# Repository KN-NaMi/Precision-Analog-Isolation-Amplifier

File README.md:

# Precision-Analog-Isolation-Amplifier

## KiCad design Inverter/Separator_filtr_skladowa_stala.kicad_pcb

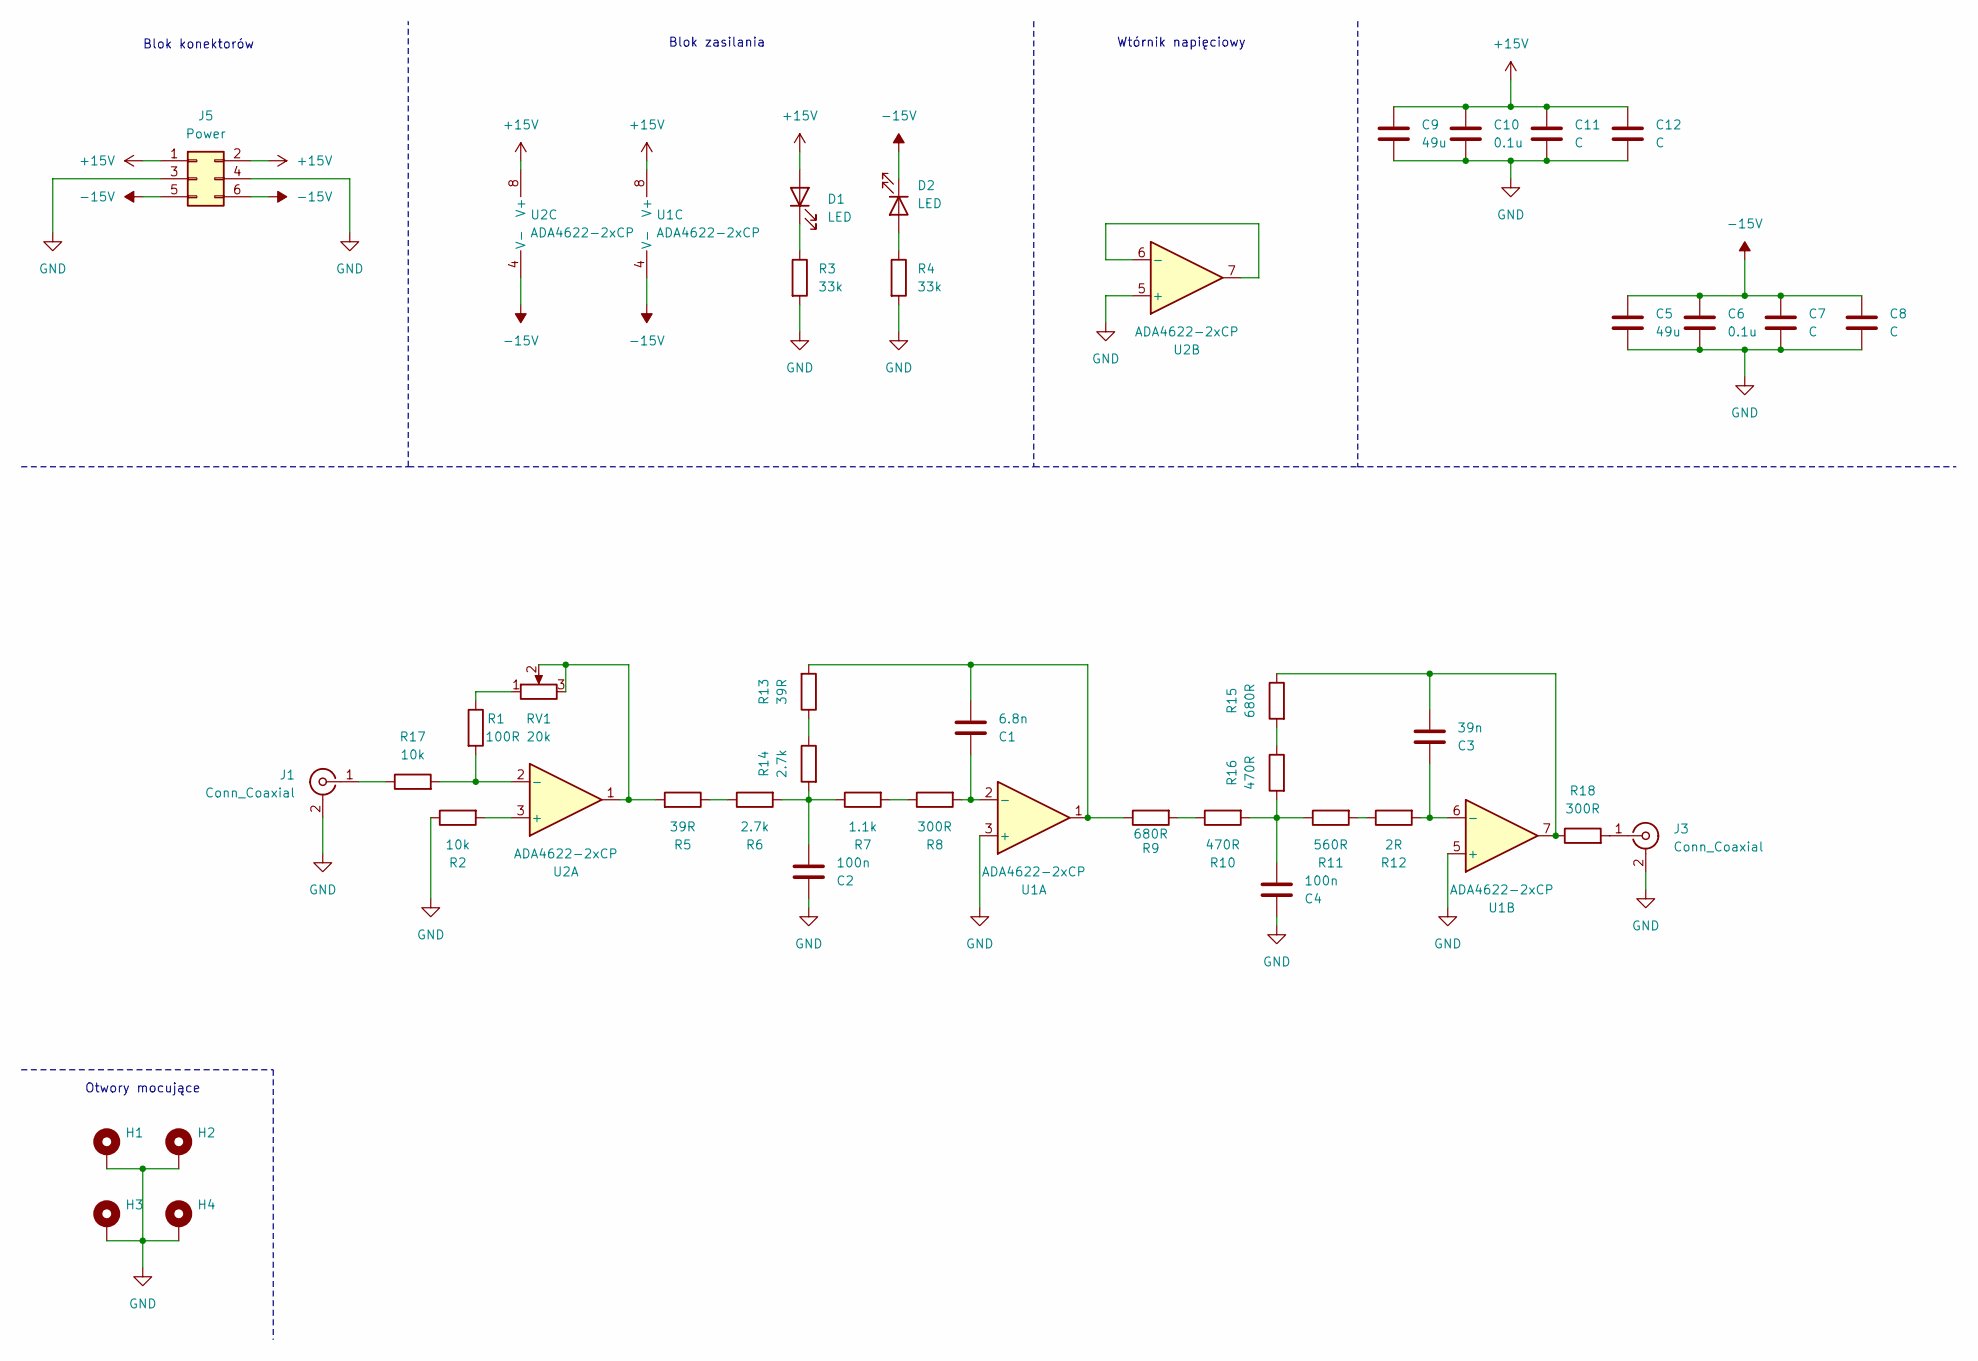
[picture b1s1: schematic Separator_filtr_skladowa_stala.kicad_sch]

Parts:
C1: 6.8n; C_0805_2012Metric_Pad1.18x1.45mm_HandSolder
C2, C4: 100n; C_0805_2012Metric_Pad1.18x1.45mm_HandSolder
C3: 39n; C_0805_2012Metric_Pad1.18x1.45mm_HandSolder
C5, C9: 49u; C_0805_2012Metric_Pad1.18x1.45mm_HandSolder
C6, C10: 0.1u; C_0805_2012Metric_Pad1.18x1.45mm_HandSolder
C7, C8, C11, C12: C; C_0805_2012Metric_Pad1.18x1.45mm_HandSolder
D1, D2: LED; LED_0805_2012Metric_Pad1.15x1.40mm_HandSolder
H1, H2, H3, H4: MountingHole_Pad; MountingHole_3.2mm_M3_DIN965_Pad
J1, J3: Conn_Coaxial; CONN_732511350_MOL
J5: Power; PinHeader_2x03_P2.54mm_Vertical
R1: 100R; R_0805_2012Metric_Pad1.20x1.40mm_HandSolder
R2, R17: 10k; R_0805_2012Metric_Pad1.20x1.40mm_HandSolder
R3, R4: 33k; R_0805_2012Metric_Pad1.20x1.40mm_HandSolder
R5, R13: 39R; R_0805_2012Metric_Pad1.20x1.40mm_HandSolder
R6, R14: 2.7k; R_0805_2012Metric_Pad1.20x1.40mm_HandSolder
R7: 1.1k; R_0805_2012Metric_Pad1.20x1.40mm_HandSolder
R8, R18: 300R; R_0805_2012Metric_Pad1.20x1.40mm_HandSolder
R9, R15: 680R; R_0805_2012Metric_Pad1.20x1.40mm_HandSolder
R10, R16: 470R; R_0805_2012Metric_Pad1.20x1.40mm_HandSolder
R11: 560R; R_0805_2012Metric_Pad1.20x1.40mm_HandSolder
R12: 2R; R_0805_2012Metric_Pad1.20x1.40mm_HandSolder
RV1: 20k; Potentiometer_Bourns_3386W_Horizontal
U1, U2: ADA4622-2xCP; SOIC127P600X175-8N

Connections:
+15V: C9.1, C10.1, C11.1, C12.1, D1.2 (A), J5.1, J5.2, U1.8 (V+), U1.9 (V+), U2.8 (V+), U2.9 (V+)
-15V: C5.1, C6.1, C7.1, C8.1, D2.1 (K), J5.5, J5.6, U1.4 (V-), U2.4 (V-)
GND: C2.1, C4.1, C5.2, C6.2, C7.2, C8.2, C9.2, C10.2, C11.2, C12.2, H1.1, H2.1, H3.1, H4.1, J1.2 (Ext), J1.3, J1.4, J1.5, J3.2 (Ext), J3.3, J3.4, J3.5, J5.3, J5.4, R2.1, R3.2, R4.2, U1.3 (+), U1.5 (+), U2.5 (+)
unnamed: C1.2, R9.1, R13.2, U1.1
unnamed: C2.2, R6.2, R7.1, R14.2
unnamed: C3.2, R15.1, R18.1, U1.7
unnamed: C4.2, R10.2, R11.1, R16.2
unnamed: D1.1 (K), R3.1
unnamed: D2.2 (A), R4.1
unnamed: J1.1 (In), R17.1
unnamed: J3.1 (In), R18.2
unnamed: R1.1, RV1.1
unnamed: R5.1, R6.1
unnamed: R5.2, RV1.2, RV1.3, U2.1
unnamed: R7.2, R8.1
unnamed: R9.2, R10.1
unnamed: R11.2, R12.1
unnamed: R13.1, R14.1
unnamed: R15.2, R16.1
unnamed: C1.1, R8.2, U1.2 (-)
unnamed: C3.1, R12.2, U1.6 (-)
unnamed: R2.2, U2.3 (+)
unnamed: R1.2, R17.2, U2.2 (-)
unnamed: U2.6 (-), U2.7

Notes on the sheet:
Otwory mocujące
Blok zasilania
Wtórnik napięciowy
Blok konektorów

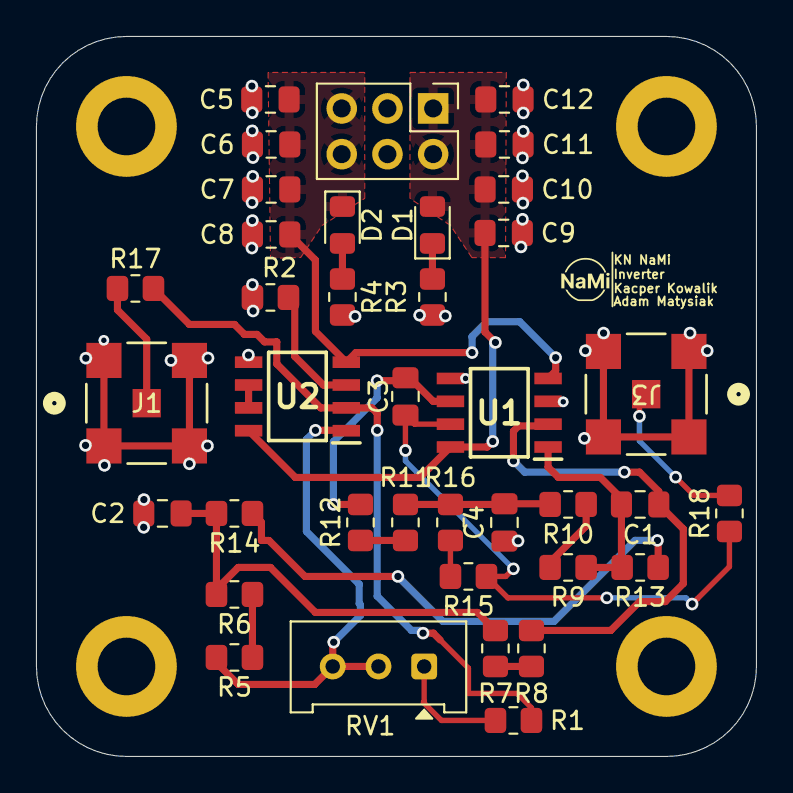
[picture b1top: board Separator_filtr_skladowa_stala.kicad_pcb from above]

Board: 2 copper layers, 40.0 x 40.0 mm, 42 parts (0 on the bottom side), 24 nets.

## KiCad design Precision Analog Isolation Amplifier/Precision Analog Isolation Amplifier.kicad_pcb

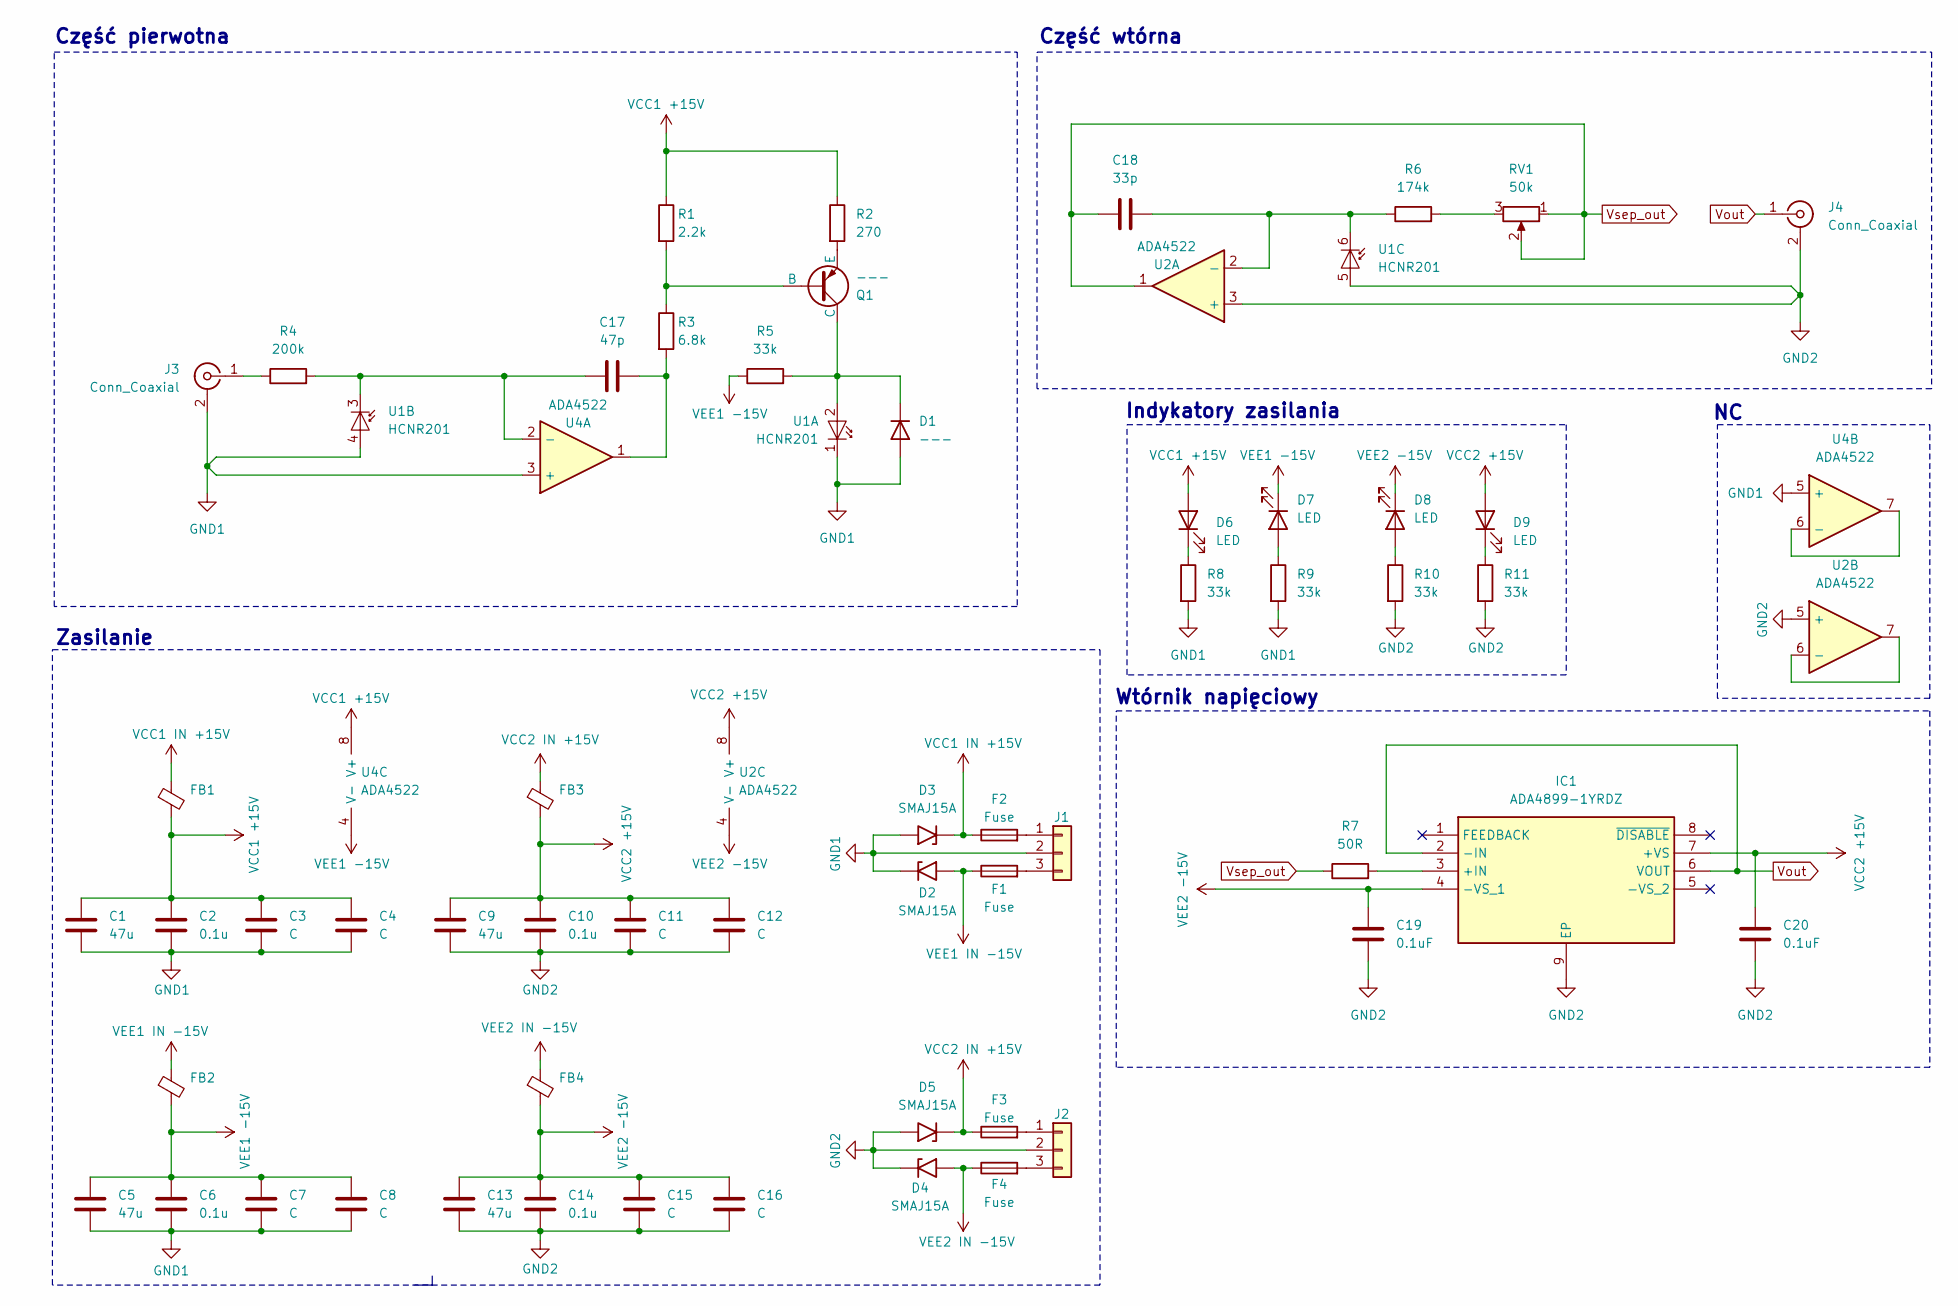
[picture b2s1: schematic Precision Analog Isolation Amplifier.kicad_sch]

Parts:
C1, C5, C9, C13: 47u; C_0805_2012Metric_Pad1.18x1.45mm_HandSolder
C2, C6, C10, C14: 0.1u; C_0805_2012Metric_Pad1.18x1.45mm_HandSolder
C3, C4, C7, C8, C11, C12, C15, C16: C; C_0805_2012Metric_Pad1.18x1.45mm_HandSolder
C17: 47p; C_0805_2012Metric_Pad1.18x1.45mm_HandSolder
C18: 33p; C_0805_2012Metric_Pad1.18x1.45mm_HandSolder
C19, C20: 0.1uF; C_0805_2012Metric_Pad1.18x1.45mm_HandSolder
D1: ---; D_0805_2012Metric_Pad1.15x1.40mm_HandSolder
D2, D3, D4, D5: SMAJ15A; D_SMA
D6, D7, D8, D9: LED; D_0805_2012Metric_Pad1.15x1.40mm_HandSolder
F1, F2, F3, F4: Fuse; R_0805_2012Metric_Pad1.20x1.40mm_HandSolder
FB1, FB2, FB3, FB4: FerriteBead_Small; L_1206_3216Metric
IC1: ADA4899-1YRDZ; SOIC127P600X175-9N; Mouser Part Number 584-ADA4899-1YRDZ
J1, J2: Conn_01x03; PinHeader_1x03_P2.54mm_Vertical
J3, J4: Conn_Coaxial; CONN_732511350_MOL
Q1: ---; SOT-23_Handsoldering
R1: 2.2k; R_0805_2012Metric_Pad1.20x1.40mm_HandSolder
R2: 270; R_0805_2012Metric_Pad1.20x1.40mm_HandSolder
R3: 6.8k; R_0805_2012Metric_Pad1.20x1.40mm_HandSolder
R4: 200k; R_0805_2012Metric_Pad1.20x1.40mm_HandSolder
R5, R8, R9, R10, R11: 33k; R_0805_2012Metric_Pad1.20x1.40mm_HandSolder
R6: 174k; R_0805_2012Metric_Pad1.20x1.40mm_HandSolder
R7: 50R; R_0805_2012Metric_Pad1.20x1.40mm_HandSolder
RV1: 50k; Potentiometer_Bourns_3386W_Horizontal
U1: HCNR201; HCNR201300E
U2, U4: ADA4522; SOIC127P600X175-8N

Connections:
GND1: C1.1, C2.1, C3.1, C4.1, C5.1, C6.1, C7.1, C8.1, D1.2 (A), D2.1 (A1), D3.2 (A2), J1.2, J3.2 (Ext), J3.3, J3.4, J3.5, R8.2, R9.2, U1.1 (K), U1.4 (A), U4.3 (+), U4.5 (+)
GND2: C9.1, C10.1, C11.1, C12.1, C13.1, C14.1, C15.1, C16.1, C19.1, C20.1, D4.1 (A1), D5.2 (A2), IC1.9 (EP), J2.2, J4.2 (Ext), J4.3, J4.4, J4.5, R10.2, R11.2, U1.5 (A), U2.3 (+), U2.5 (+)
unnamed: C17.2, R3.2, U4.1
unnamed: D1.1 (K), Q1.1 (C), R5.2, U1.2 (A)
unnamed: D6.1 (K), R8.1
unnamed: D7.2 (A), R9.1
unnamed: D8.2 (A), R10.1
unnamed: D9.1 (K), R11.1
unnamed: IC1.3 (+IN), R7.2
unnamed: F2.2, J1.1
unnamed: F1.2, J1.3
unnamed: F3.2, J2.1
unnamed: F4.2, J2.3
unnamed: J3.1 (In), R4.1
unnamed: Q1.2 (B), R1.2, R3.1
unnamed: Q1.3 (E), R2.2
unnamed: R6.2, RV1.3
unnamed: C17.1, R4.2, U1.3 (K), U4.2 (-)
unnamed: C18.2, R6.1, U1.6 (K), U2.2 (-)
unnamed: U2.6 (-), U2.7
unnamed: U4.6 (-), U4.7
VCC1 +15V: C1.2, C2.2, C3.2, C4.2, D6.2 (A), FB1.2, R1.1, R2.1, U4.8 (V+)
VCC1 IN +15V: D3.1 (A1), F2.1, FB1.1
VCC2 +15V: C9.2, C10.2, C11.2, C12.2, C20.2, D9.2 (A), FB3.2, IC1.7 (+VS), U2.8 (V+)
VCC2 IN +15V: D5.1 (A1), F3.1, FB3.1
VEE1 -15V: C5.2, C6.2, C7.2, C8.2, D7.1 (K), FB2.2, R5.1, U4.4 (V-)
VEE1 IN -15V: D2.2 (A2), F1.1, FB2.1
VEE2 -15V: C13.2, C14.2, C15.2, C16.2, C19.2, D8.1 (K), FB4.2, IC1.4 (-VS_1), U2.4 (V-)
VEE2 IN -15V: D4.2 (A2), F4.1, FB4.1
Vout: IC1.2 (-IN), IC1.6 (VOUT), J4.1 (In)
Vsep_out: C18.1, R7.1, RV1.1, RV1.2, U2.1

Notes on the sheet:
Zasilanie
Część pierwotna
Wtórnik napięciowy
Indykatory zasilania
Część wtórna

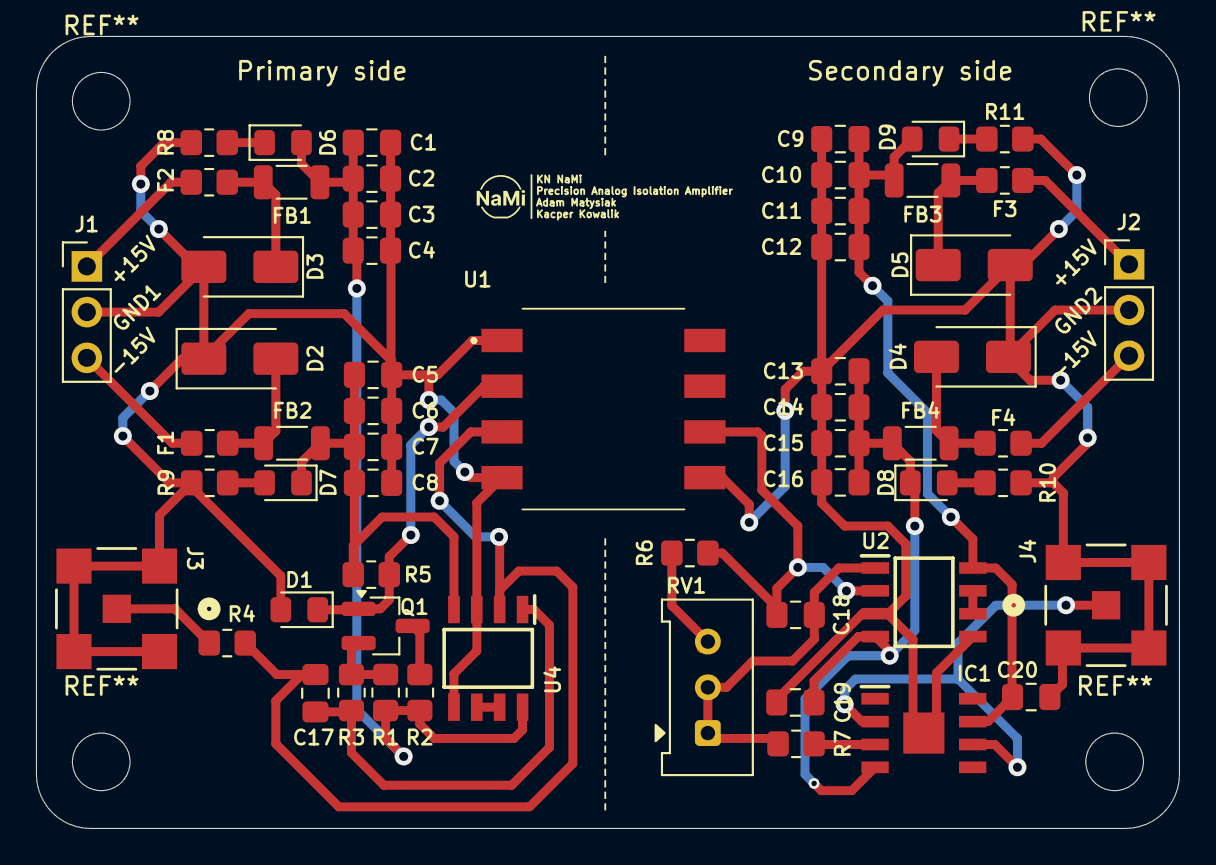
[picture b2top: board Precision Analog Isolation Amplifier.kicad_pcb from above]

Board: 2 copper layers, 63.5 x 44.0 mm, 58 parts (0 on the bottom side), 31 nets.

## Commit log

2025-05-24 Init
2025-06-03 Add few components & Start PCB design
2025-06-07 Update Schematic & PCB
2025-06-11 Change libraries from global to project specific
2025-06-11 Update PCB
2025-06-11 Update PCB layout
2025-06-12 Update Schematic and Add Tracks to PCB
2025-07-05 Edit Silkscreen
2025-07-08 Update PCB & Schematic
2025-10-27 Add inverter schematic + pcb
    Added inverter and filter (fc=3kHz) schematic + pcb
2025-10-27 pcb update
2025-11-01 Edit PCB
2025-11-07 pcb final version
2025-11-07 Add LTSpice simulation
